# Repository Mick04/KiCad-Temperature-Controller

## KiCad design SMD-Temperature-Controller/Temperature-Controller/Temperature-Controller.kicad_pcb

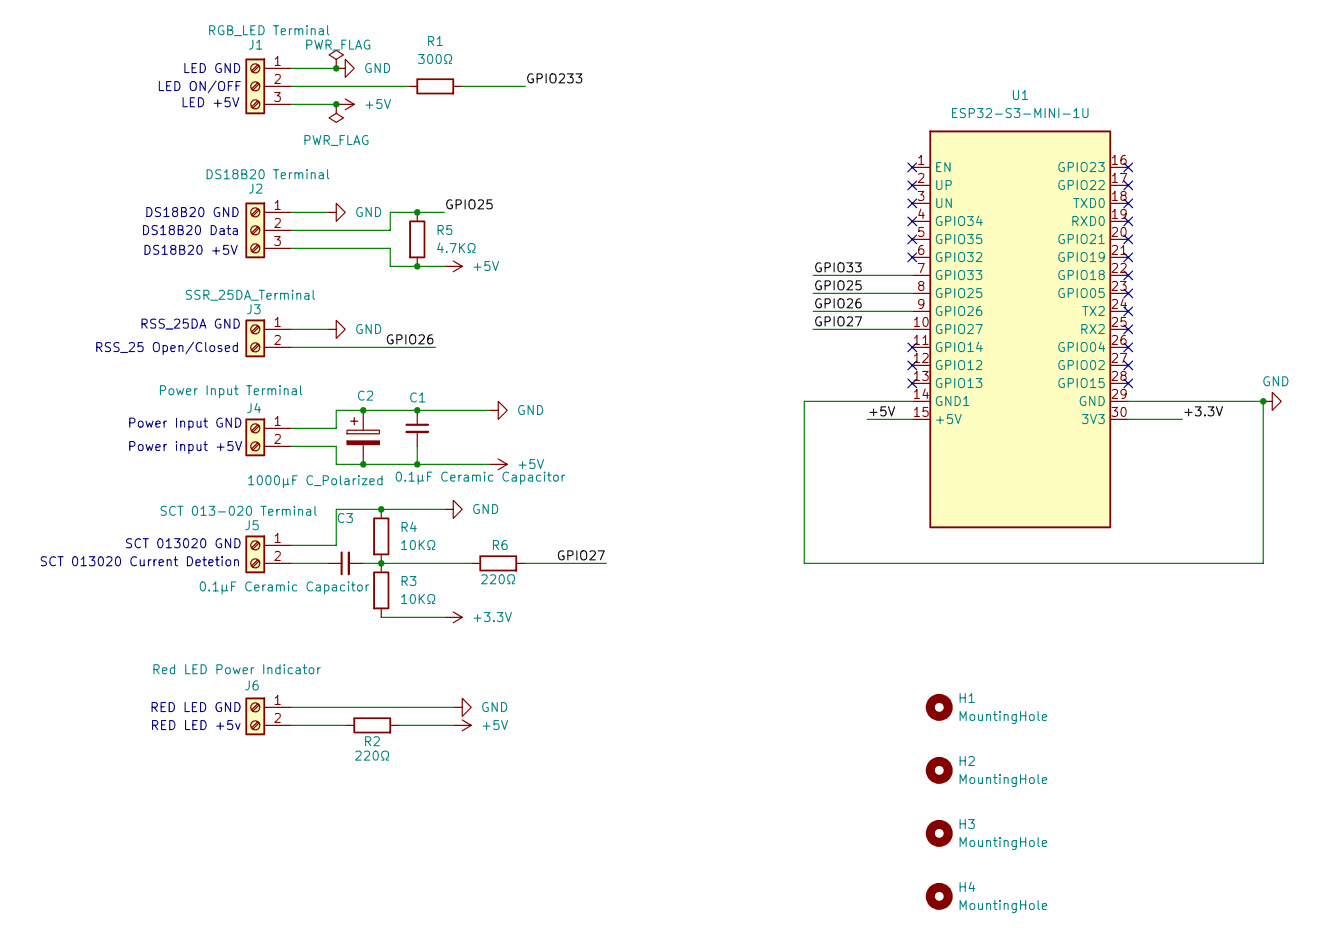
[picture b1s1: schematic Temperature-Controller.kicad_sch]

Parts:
C1, C3: 0.1µF Ceramic Capacitor; C_Disc_D3.0mm_W1.6mm_P2.50mm; Part Number C49678
C2: 1000µF C_Polarized; CP_Elec_8x10.5; Part number C330210
H1, H2, H3, H4: MountingHole; MountingHole_3.2mm_M3_ISO7380
J1: RGB_LED Terminal; TerminalBlock_bornier-3_P5.08mm
J2: DS18B20 Terminal; TerminalBlock_bornier-3_P5.08mm
J3: SSR_25DA_Terminal; TerminalBlock_4Ucon_1x02_P3.50mm_Horizontal
J4: Power Input Terminal; TerminalBlock_4Ucon_1x02_P3.50mm_Horizontal
J5: SCT 013-020 Terminal; TerminalBlock_4Ucon_1x02_P3.50mm_Horizontal
J6: Red LED Power Indicator; TerminalBlock_4Ucon_1x02_P3.50mm_Horizontal
R1: 300Ω; R_0805_2012Metric
R2, R6: 220Ω; R_0805_2012Metric
R3, R4: 10KΩ; R_0805_2012Metric
R5: 4.7KΩ; R_0805_2012Metric
U1: ESP32-S3-MINI-1U; ESP32-S2-MINI-1U

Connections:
+3.3V: R3.2, U1.30 (3V3)
+5V: C1.2, C2.2, J1.3, J2.3, J4.2, R2.2, R5.2, U1.15 (+5V)
/GPIO25: J2.2, R5.1, U1.8 (GPIO25)
/GPIO26: J3.2, U1.9 (GPIO26)
/GPIO27: R6.2, U1.10 (GPIO27)
/GPIO33: U1.7 (GPIO33)
/GPIO233: R1.2
GND: C1.1, C2.1, J1.1, J2.1, J3.1, J4.1, J5.1, J6.1, R4.1, U1.14 (GND1), U1.29 (GND)
unnamed: C3.2, R3.1, R4.2, R6.1
unnamed: J1.2, R1.1
unnamed: C3.1, J5.2
unnamed: J6.2, R2.1

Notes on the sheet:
RSS_25DA GND
DS18B20 GND
Power Input GND
SCT 013020 Current Detetion
RSS_25 Open/Closed
LED GND
LED +5V
Power input +5V
DS18B20 Data
LED ON/OFF
RED LED GND
DS18B20 +5V
RED LED +5v
SCT 013020 GND

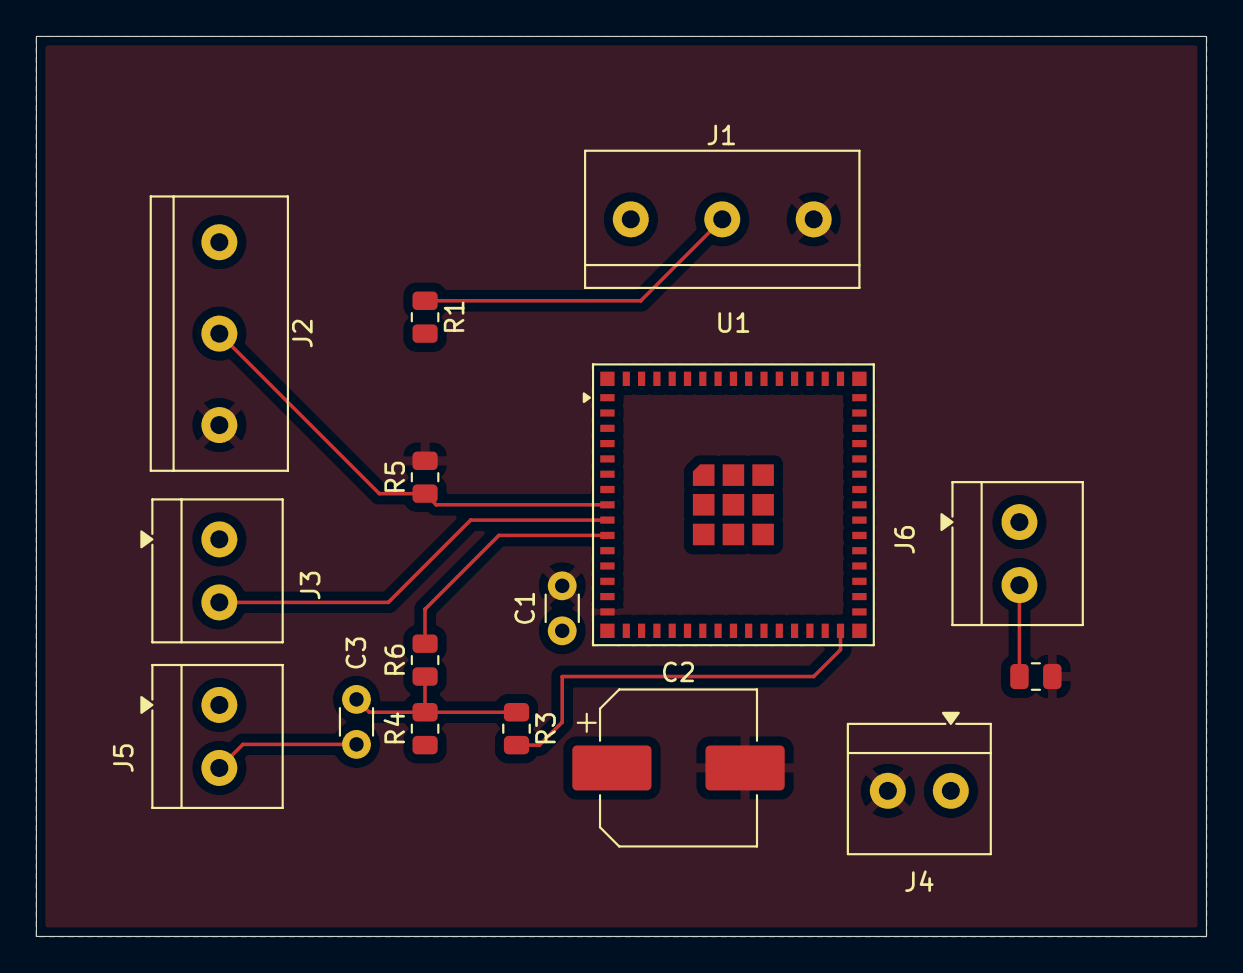
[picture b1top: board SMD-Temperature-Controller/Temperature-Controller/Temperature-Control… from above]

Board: 2 copper layers, 65.0 x 50.0 mm, 20 parts (0 on the bottom side), 10 nets.

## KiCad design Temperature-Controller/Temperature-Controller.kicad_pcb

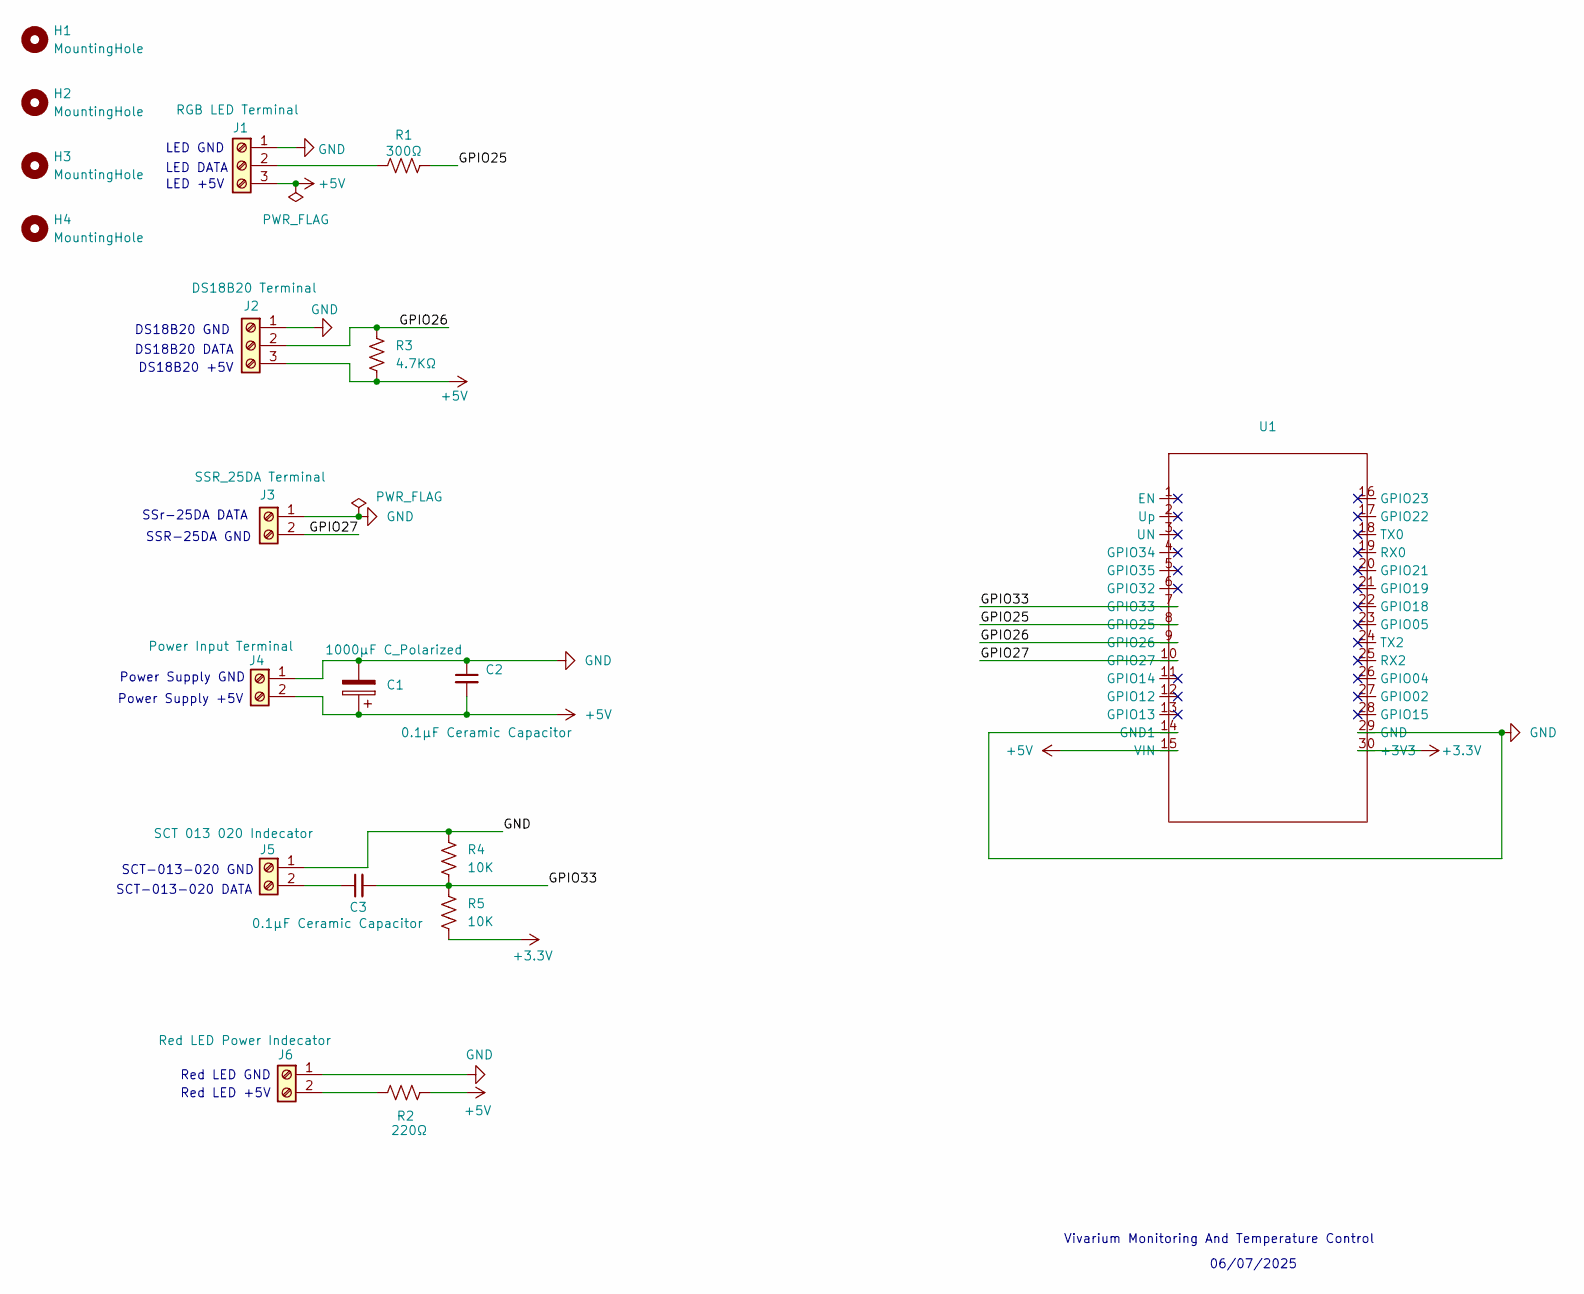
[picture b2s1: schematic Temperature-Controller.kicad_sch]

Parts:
C1: 1000µF C_Polarized; CP_Radial_D8.0mm_P2.50mm
C2, C3: 0.1µF Ceramic Capacitor; C_Disc_D3.0mm_W1.6mm_P2.50mm
H1, H2, H3, H4: MountingHole; MountingHole_3.2mm_M3_ISO7380
J1: RGB LED Terminal; TerminalBlock_bornier-3_P5.08mm
J2: DS18B20 Terminal; TerminalBlock_bornier-3_P5.08mm
J3: SSR_25DA Terminal; TerminalBlock_bornier-2_P5.08mm
J4: Power Input Terminal; TerminalBlock_bornier-2_P5.08mm
J5: SCT 013 020 Indecator; TerminalBlock_bornier-2_P5.08mm
J6: Red LED Power Indecator; TerminalBlock_bornier-2_P5.08mm
R1: 300Ω; R_Axial_DIN0207_L6.3mm_D2.5mm_P7.62mm_Horizontal
R2: 220Ω; R_Axial_DIN0207_L6.3mm_D2.5mm_P7.62mm_Horizontal
R3: 4.7KΩ; R_Axial_DIN0207_L6.3mm_D2.5mm_P7.62mm_Horizontal
R4, R5: 10K; R_Axial_DIN0207_L6.3mm_D2.5mm_P7.62mm_Horizontal
U1: ESP32-DevKit

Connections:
+3.3V: R5.1, U1.30 (+3V3)
+5V: C1.1, C2.2, J1.3, J2.3, J4.2, R2.2, R3.1, U1.15 (VIN)
/GPIO25: R1.2, U1.8 (GPIO25)
/GPIO26: J2.2, R3.2, U1.9 (GPIO26)
/GPIO27: J3.2, U1.10 (GPIO27)
/GPIO33: C3.2, R4.1, R5.2, U1.7 (GPIO33)
GND: C1.2, C2.1, J1.1, J2.1, J3.1, J4.1, J5.1, J6.1, R4.2, U1.14 (GND1), U1.29 (GND)
unnamed: J1.2, R1.1
unnamed: C3.1, J5.2
unnamed: J6.2, R2.1

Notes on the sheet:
Vivarium Monitoring And Temperature Control
DS18B20 DATA
SCT-013-020 GND
Red LED GND
SSR-25DA GND
Red LED +5V
DS18B20 +5V
SSr-25DA DATA
SCT-013-020 DATA
LED GND
LED DATA
06/07/2025
Power Supply +5V
Power Supply GND
DS18B20 GND
LED +5V

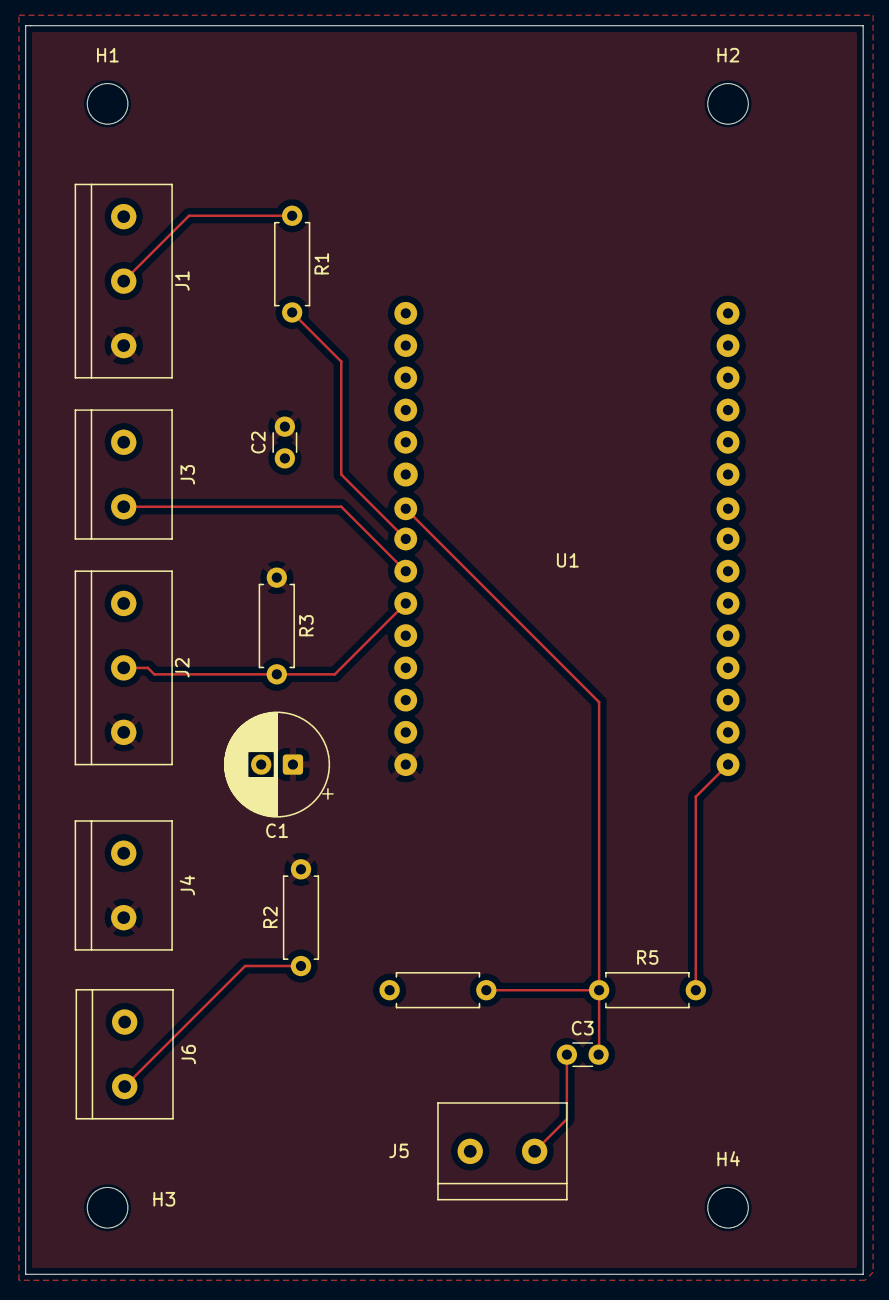
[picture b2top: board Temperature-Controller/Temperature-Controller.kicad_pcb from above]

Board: 2 copper layers, 66.0 x 98.4 mm, 19 parts (0 on the bottom side), 10 nets.

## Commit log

2025-07-09 Gerber files added
2025-07-13 Corrected the schematic for the SCT 013 020 sensor
2025-07-17 Ready for creating the Gerber files
2025-07-18 Last commit before changing terminals
